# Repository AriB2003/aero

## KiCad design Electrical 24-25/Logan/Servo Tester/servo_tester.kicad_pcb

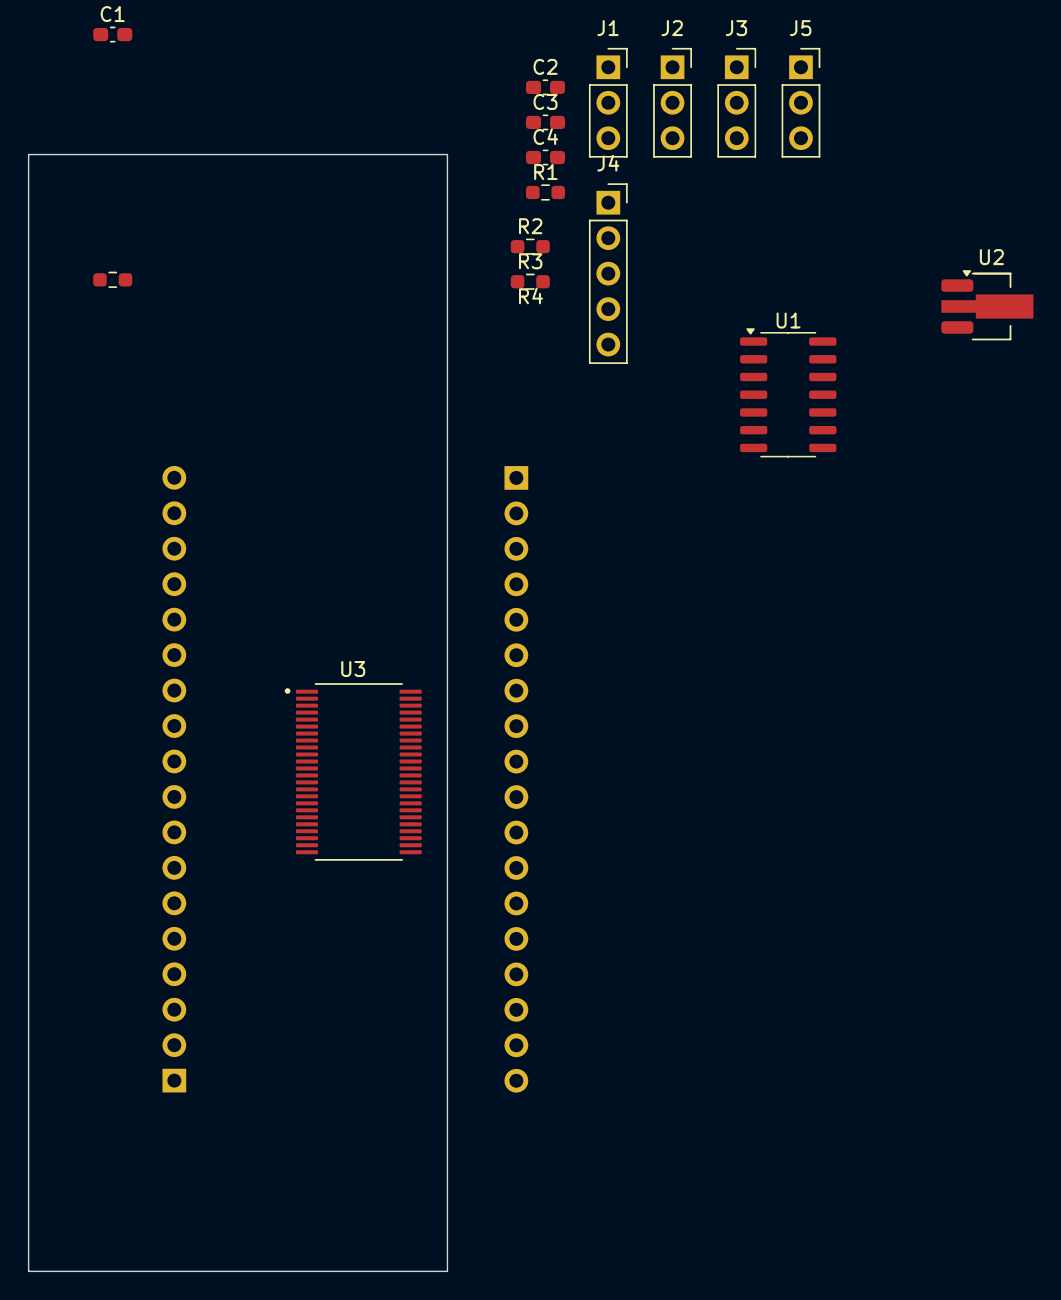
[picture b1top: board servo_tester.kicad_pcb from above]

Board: 2 copper layers, 30.0 x 80.0 mm, 17 parts (1 on the bottom side), 48 nets, no tracks yet.

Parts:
C1: 1u; C_0603_1608Metric_Pad1.08x0.95mm_HandSolder
C2: 2.2u; C_0603_1608Metric_Pad1.08x0.95mm_HandSolder
C3, C4: 100n; C_0603_1608Metric_Pad1.08x0.95mm_HandSolder
J1: Servo 1; PinSocket_1x03_P2.54mm_Vertical
J2: Servo 2; PinSocket_1x03_P2.54mm_Vertical
J3: Power In; PinSocket_1x03_P2.54mm_Vertical
J4: Prog; PinSocket_1x05_P2.54mm_Vertical
J5: Servo 3; PinSocket_1x03_P2.54mm_Vertical
R1, R2, R4: 4.7k; R_0603_1608Metric_Pad0.98x0.95mm_HandSolder
R3: 15k; R_0603_1608Metric_Pad0.98x0.95mm_HandSolder
U1: ATtiny404-SS; SOIC-14_3.9x8.7mm_P1.27mm
U2: AP2205-33Y-13; SOT-89-3_Handsoldering
U3: PCF8551ATT_AJ; SOP50P810X120-48N
U4: VIM-878-DP-FC-S-LV; VIM-878-DP

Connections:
3V3: C2.1, C3.1, C4.1, J4.2, R1.1, R2.1, U1.1 (VCC), U2.3 (OUT), U3.10 (VLCD), U3.11 (VDD), U3.17 (PORE)
/0: U3.18 (SEG0), U4.27 (DP5/5C/5B/5A)
/1: U3.19 (SEG1), U4.26 (6M/6N/6G/6H)
/2: U3.20 (SEG2), U4.25 (DP6/6C/6B/6A)
/3: U3.21 (SEG3), U4.24 (7M/7N/7G/7H)
/4: U3.22 (SEG4), U4.23 (DP7/7C/7B/7A)
/5: U3.23 (SEG5), U4.22 (8M/8N/8G/8H)
/6: U3.24 (SEG6), U4.21 (DP8/8C/8B/8A)
/7: U3.25 (SEG7), U4.16 (8L/8K/8J/8I)
/8: U3.26 (SEG8), U4.15 (8D/8E/8F/CA8)
/9: U3.27 (SEG9), U4.14 (7L/7K/7J/7I)
/10: U3.28 (SEG10), U4.13 (7D/7E/7F/CA7)
/11: U3.29 (SEG11), U4.12 (6L/6K/6J/6I)
/12: U3.30 (SEG12), U4.11 (6D/6E/6F/CA6)
/13: U3.31 (SEG13), U4.10 (5L/5K/5J/5I)
/14: U3.32 (SEG14), U4.9 (5D/5E/5F/CA5)
/15: U3.33 (SEG15), U4.8 (4L/4K/4J/4I)
/16: U3.34 (SEG16), U4.7 (4D/4E/4F/CA4)
/17: U3.35 (SEG17), U4.6 (3L/3K/3J/3I)
/18: U3.36 (SEG18), U4.5 (3D/3E/3F/CA3)
/19: U3.37 (SEG19), U4.4 (2L/2K/2J/2I)
/20: U3.38 (SEG20), U4.3 (2D/2E/2F/CA2)
/21: U3.39 (SEG21), U4.2 (1L/1K/1J/1I)
/22: U3.40 (SEG22), U4.1 (1D/1E/1F/CA1)
/27: U3.45 (SEG27), U4.33 (DP1/2C/2B/2A)
/28: U3.46 (SEG28), U4.34 (2M/2N/2G/2H)
/29: U3.47 (SEG29), U4.35 (DP1/1C/1B/1A)
/30: U3.48 (SEG30), U4.36 (1M/1N/1G/1H)
/31: U3.1 (SEG31), U4.32 (3M/3N/3G/3H)
/32: U3.2 (SEG32), U4.31 (DP3/3C/3B/3A)
/33: U3.3 (SEG33), U4.30 (4M/4N/4G/4H)
/34: U3.4 (SEG34), U4.29 (DP4/4C/4B/4A)
/35: U3.5 (SEG35), U4.28 (5M/5N/5G/5H)
/COM0: U3.6 (COM0), U4.17 (COM0)
/COM1: U3.7 (COM1), U4.18 (COM1)
/COM2: U3.8 (COM2), U4.19 (COM2)
/COM3: U3.9 (COM3), U4.20 (COM3)
/PWM1: J1.1, U1.3 (PA5)
/PWM2: J2.1, U1.2 (PA4)
/PWM3: J5.1, U1.13 (PA3)
/SCL: R2.2, U1.9 (PB0), U3.15 (SCL)
/SDA: R1.2, U1.8 (PB1), U3.16 (SDA)
/UART_RX: J4.4, U1.6 (PB3)
/UART_TX: J4.5, U1.7 (PB2)
/UPDI: J4.1, U1.10 (~RESET/PA0)
/VREAD: R3.2, R4.1, U1.5 (PA7)
GND: C1.2, C2.2, C3.2, C4.2, J1.3, J2.3, J3.3, J4.3, J5.3, R4.2, U1.14 (GND), U2.2 (GND), U3.12 (VSS), U3.13 (T1)
VIN: C1.1, J1.2, J2.2, J3.2, J5.2, R3.1, U2.1 (IN)
